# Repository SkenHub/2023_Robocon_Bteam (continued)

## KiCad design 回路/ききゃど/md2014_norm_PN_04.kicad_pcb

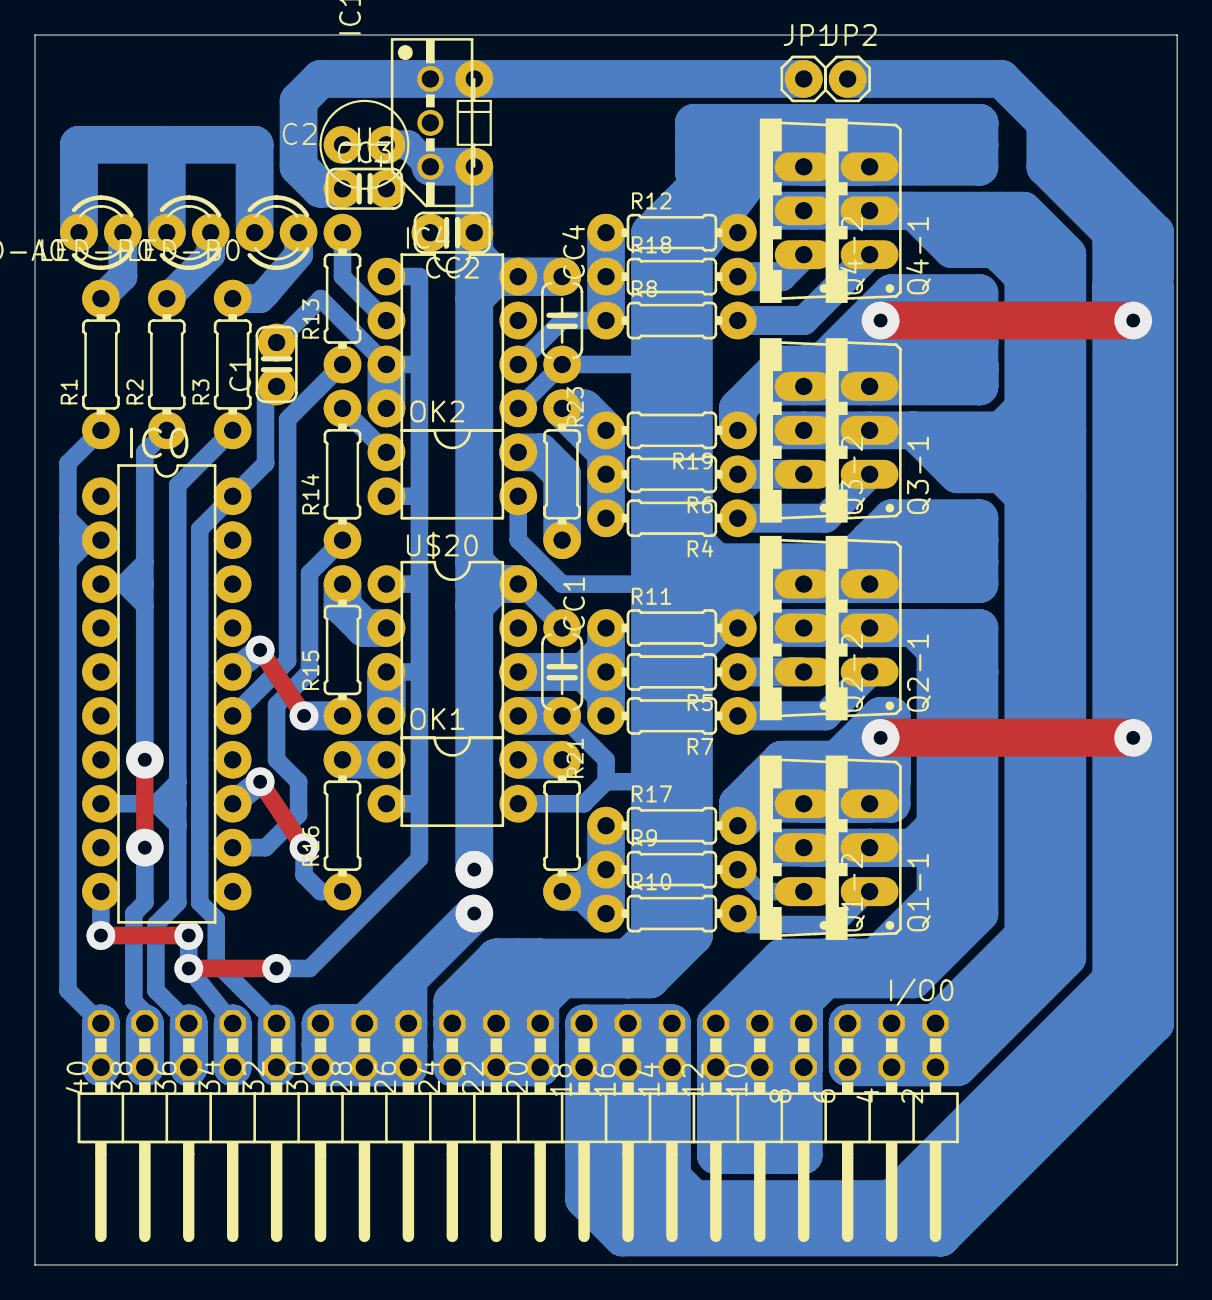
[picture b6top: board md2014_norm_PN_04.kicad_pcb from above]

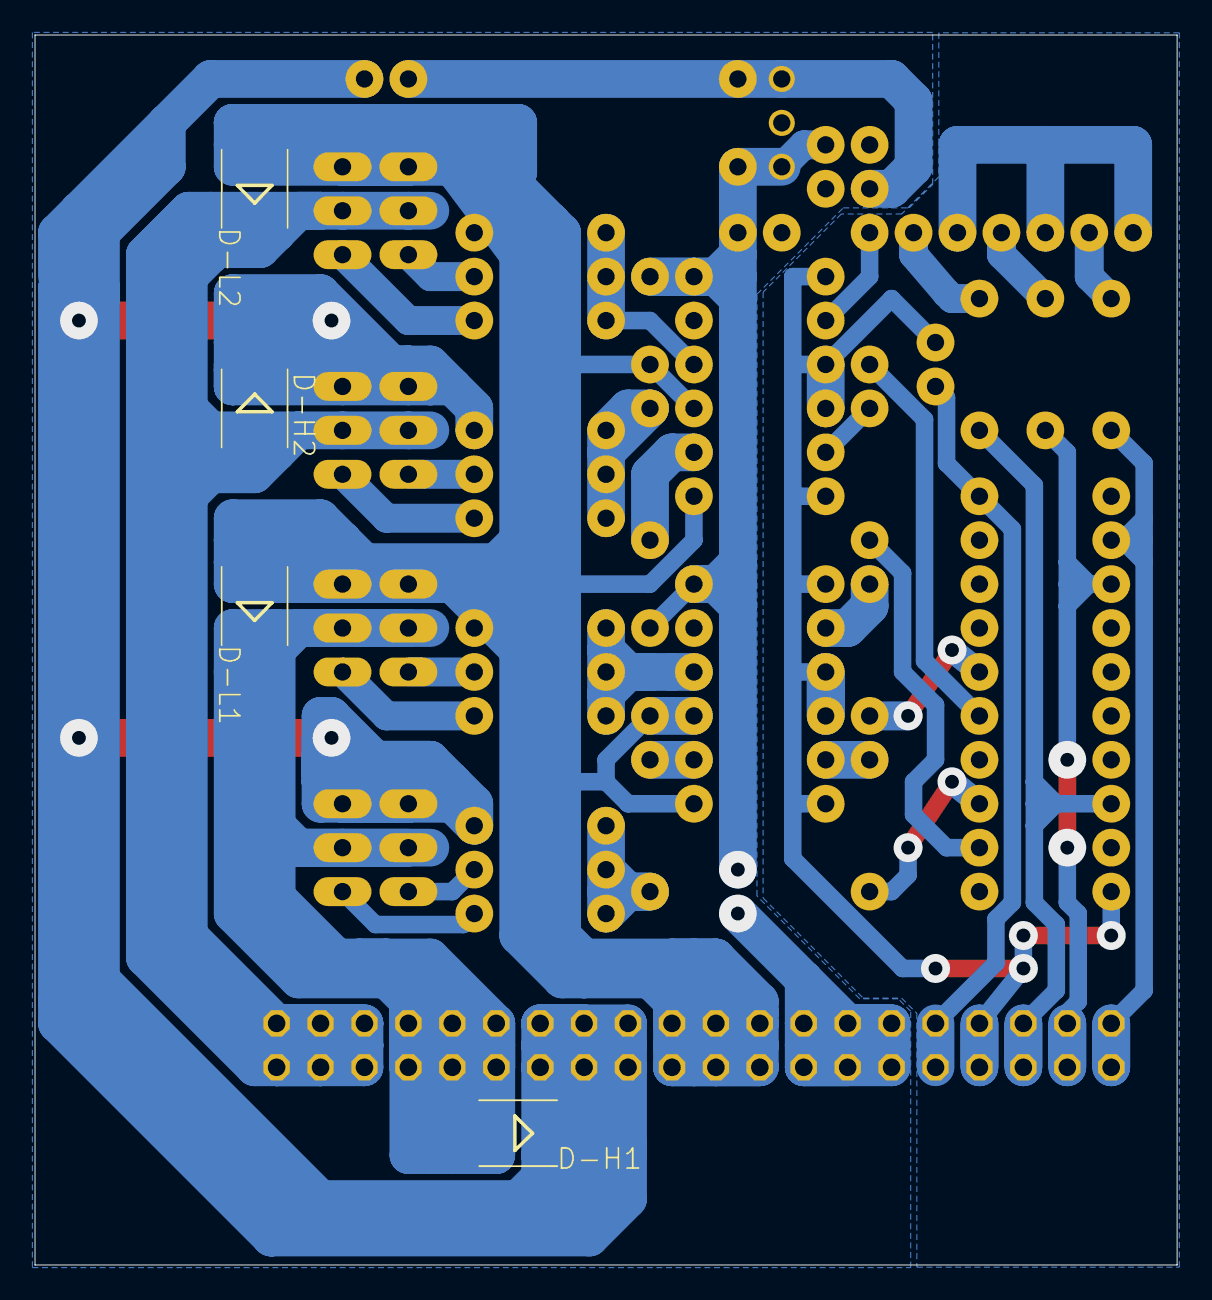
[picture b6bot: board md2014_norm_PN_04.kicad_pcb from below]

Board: 16 copper layers, 66.0 x 71.1 mm, 52 parts (4 on the bottom side), 37 nets.

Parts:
C1: 0.1uF; MLCC_25
C2: C_1U
CC1, CC4: 0.1uF; MLCC_50
CC2, CC3: 0.1uF; MLCC_25
D1: DIODE_3
D-H1, D-H2: SMB
D-L1, D-L2: SMB
I/O0: MA20-2W
IC0: ATtiny2313; DIL20
IC1: 78XX
IC4: TLP351; DIP8
JP1, JP2: 1X01
LED-A0: LED3MM
LED-B0: LED3MM
LED-P0: LED3MM
OK1, OK2: TLP621; DIP4
Q1-1, Q1-2: IRF4905; TO-220V
Q2-1, Q2-2, Q4-1, Q4-2: N; TO-220V
Q3-1, Q3-2: P; TO-220V
R1, R2, R3: 510; R_0.3
R4, R5, R6, R7, R8, R9, R10, R18: 100; R_0.3
R11, R12: 5.1k; R_0.3
R13, R14, R15, R16: 330; R_0.3
R17, R19, R21, R23: 2.2k; R_0.3
U$20: TLP251; DIP8

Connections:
+5V: C1.1, I/O0.31, I/O0.32, IC0.20
+12V: C2.P$1, CC1.1, CC2.1, CC4.1, D1.A, IC1.P$3, IC4.8, U$20.8
+24V: D-H1.C, D-H2.C, I/O0.13, I/O0.14, I/O0.15, I/O0.16, I/O0.17, I/O0.18, JP2.1, Q1-1.3, Q1-2.3, Q3-1.3, Q3-2.3, R17.2, R19.1
A-OUT: D-H2.A, D-L2.C, I/O0.1, I/O0.2, I/O0.3, I/O0.4, I/O0.5, I/O0.6, Q3-1.2, Q3-2.2, Q4-1.2, Q4-2.2
A-SIG: I/O0.39, I/O0.40, IC0.2, R1.1
B-OUT: D-H1.A, D-L1.C, I/O0.7, I/O0.8, I/O0.9, I/O0.10, I/O0.11, I/O0.12, Q1-1.2, Q1-2.2, Q2-1.2, Q2-2.2
B-SIG: I/O0.35, I/O0.36, IC0.8, R3.1
GND: C1.2, I/O0.33, I/O0.34, IC0.10, IC4.1, IC4.3, IC4.4, LED-A0.K, LED-B0.K, LED-P0.K, OK1.2, OK2.2, U$20.1, U$20.3, U$20.4
GND12: C2.P$2, CC1.2, CC2.2, CC3.2, CC4.2, D-L1.A, D-L2.A, I/O0.19, I/O0.20, I/O0.21, I/O0.22, I/O0.23, I/O0.24, IC1.P$2, IC4.5, OK1.3, OK2.3, Q2-1.3, Q2-2.3, Q4-1.3, Q4-2.3, R11.2, R12.2, U$20.5
H1: IC0.13, R16.1
H2: IC0.12, R14.1
L1: IC0.16, R15.1
L2: IC0.15, R13.1
unnamed: Q2-2.1, R5.1
unnamed: OK1.4, R21.1
unnamed: Q1-1.1, R10.2
unnamed: LED-P0.A, R2.2
unnamed: LED-A0.A, R1.2
unnamed: OK2.4, R23.2
unnamed: IC4.2, R13.2
unnamed: Q4-2.1, R18.2
unnamed: I/O0.25, I/O0.26, I/O0.27, I/O0.28, I/O0.29, I/O0.30
unnamed: Q2-1.1, R7.1
unnamed: Q4-1.1, R8.2
unnamed: R5.2, R7.2, R11.1, U$20.6
unnamed: R9.1, R10.1, R17.1, R21.2
unnamed: IC4.6, R8.1, R12.1, R18.1
unnamed: CC3.1, D1.C, IC1.P$1, JP1.1
unnamed: R4.2, R6.2, R19.2, R23.1
unnamed: Q3-2.1, R6.1
unnamed: OK1.1, R16.2
unnamed: Q1-2.1, R9.2
unnamed: LED-B0.A, R3.2
unnamed: Q3-1.1, R4.1
unnamed: OK2.1, R14.2
unnamed: R15.2, U$20.2
P-SIG: I/O0.37, I/O0.38, IC0.3, R2.1

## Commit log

2023-06-08 Create 機械
2023-06-08 Add files via upload
    ジャイロセンサー プログラム
2023-06-08 realsenseロボットのテストプログラム
    ロボットの旋回中心とrealsenseの中心の差を考慮
2023-06-08 テストロボット（足回り）のプログラム
2023-06-25 Create LED
2023-06-30 ヨー軸のシリアル通信出力
    ヨー軸の実数値（０～360度）を共用体で4バイト出力．
    先頭2バイトはHEX A0A0 で計6バイト
2023-06-30 Update wit901_1.ino
    oledディスプレイ搭載
2023-06-30 Update wit901_1.ino
    エラー修正
2023-06-30 Update wit901_1.ino
    表示をええ感じに
2023-06-30 パワーウィンドウからメカナムへ変更
2023-07-08 メカナム足回り
    PS3はSBDBTを使ってね
2023-07-10 Create unity
2023-08-20 完成形足回りプログラム
2023-08-27 収穫機構プログラムVer3制作
2023-08-30 get_V3のパラメータ調整
2023-10-03 足回りプログラム完成版
2023-10-03 ルールブックとFAQ
2023-10-05 足回りプログラム更新
    146行目の数字がモータのpwmだよ
2023-10-11 鋼鶴天翔の完成形
    改善の余地あり(悪足掻き)
